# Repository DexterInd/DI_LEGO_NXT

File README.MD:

Dexter Industries NXT Sensors
=====

This project contains the LEGO MINDSTORMS NXT blocks for Dexter Industries Sensors.  If you're looking [for EV3 sensors, please check here.](https://github.com/DexterInd/EV3_Dexter_Industries_Sensors)  

These files have been made available online through a [Creative Commons Attribution-ShareAlike 3.0](http://creativecommons.org/licenses/by-sa/3.0/) license.

## Participate!
Send us [feedback](http://www.dexterindustries.com/contact) or contribute to this repo!  It's all open-source software, and we'd be honored if you joined in!

## More Links

[Dexter Industries](http://www.dexterindustries.com/)

[Our Products](https://shop.dexterindustries.com/shop/)

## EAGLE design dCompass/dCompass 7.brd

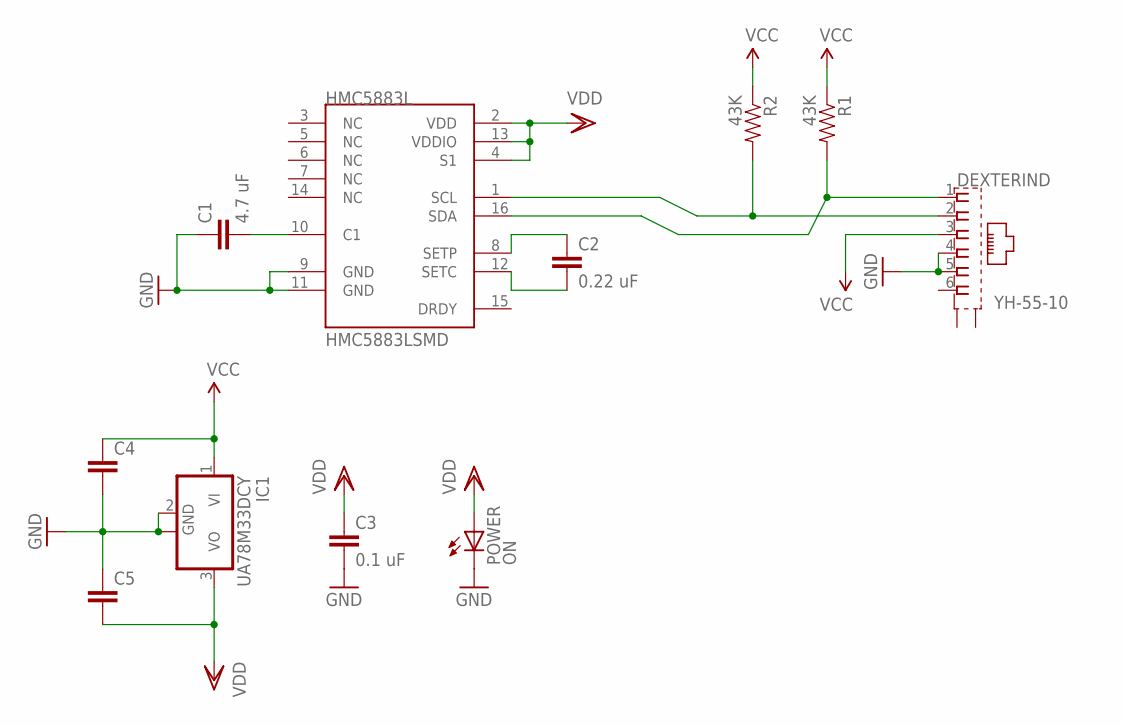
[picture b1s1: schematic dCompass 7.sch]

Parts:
C1: 4.7 uF; 0805
C2: 0.22 uF; 0805
C3: 0.1 uF; 0805
C4, C5: CAP0805; 0805
DEXTERIND: YH-55-10
HMC5883L: HMC5883LSMD; 16LPCC
IC1: UA78M33DCY; SOT223
POWER: ON; LED-1206
R1, R2: 43K; 0805

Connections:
3V3: C3.1, C5.2, HMC5883L.2 (VDD), HMC5883L.4 (S1), HMC5883L.13 (VDDIO), IC1.3 (VO), POWER.A
4V7: C4.1, DEXTERIND.3, IC1.1 (VI), R1.1, R2.1
GND: C1.1, C3.2, C4.2, C5.1, DEXTERIND.4, DEXTERIND.5, HMC5883L.9 (GND), HMC5883L.11 (GND), IC1.2 (GND), IC1.4 (GND), POWER.C
unnamed: C1.2, HMC5883L.10 (C1)
unnamed: C2.2, HMC5883L.12 (SETC)
unnamed: C2.1, HMC5883L.8 (SETP)
SCL: DEXTERIND.2, HMC5883L.1 (SCL), R2.2
SDA: DEXTERIND.1, HMC5883L.16 (SDA), R1.2

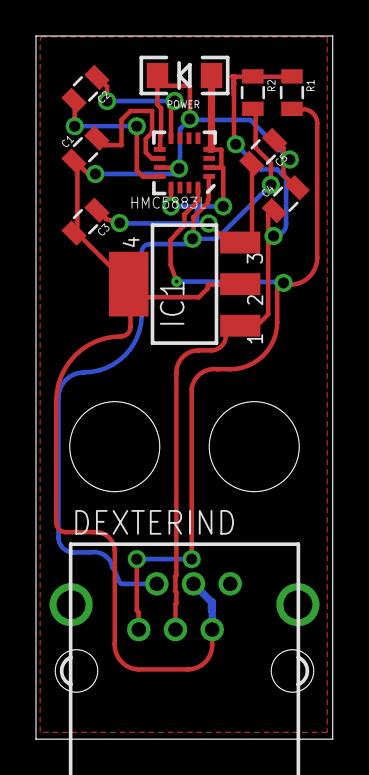
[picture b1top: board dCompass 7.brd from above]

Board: 2 copper layers, 16.5 x 39.1 mm, 11 parts (0 on the bottom side), 8 nets.

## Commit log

2015-08-06 :confetti_ball: Added .gitattributes & .gitignore files
2015-08-06 Added initial zip files.
2015-08-06 Add readme.
2015-08-06 Added Thermal infrared sensor code.
2015-08-06 Adding autonomous robotic code.
2015-08-14 dIMU Commit
    dIMU Blocks Commit
2015-08-14 Rest of the dIMU Programming Added In There
2015-08-14 Update Readme.
2015-09-01 Adding thermometer files.
2015-09-07 Adding dFlex
    dFlex information added!
2015-09-07 NXTBee Commits
2015-09-16 Adding LEGO and Arduino Code
2015-09-27 Added more pressure sensor files.
2015-10-01 Adding VI for Labview
2015-10-14 Adding dLight Examples
2015-10-22 Add GPS Controls
2016-01-19 Added datasheet for thermometers.
2016-01-20 Adding RobotC navigation to dGPS
2016-02-17 Adding LEGO Labview Code
2016-04-21 Adding Female Sockets
2016-06-23 Add dCompass Hardware
    Adding dCompass Hardware
2016-06-29 Add Breadboard Adapter Schematics
2016-06-29 Add Readme
